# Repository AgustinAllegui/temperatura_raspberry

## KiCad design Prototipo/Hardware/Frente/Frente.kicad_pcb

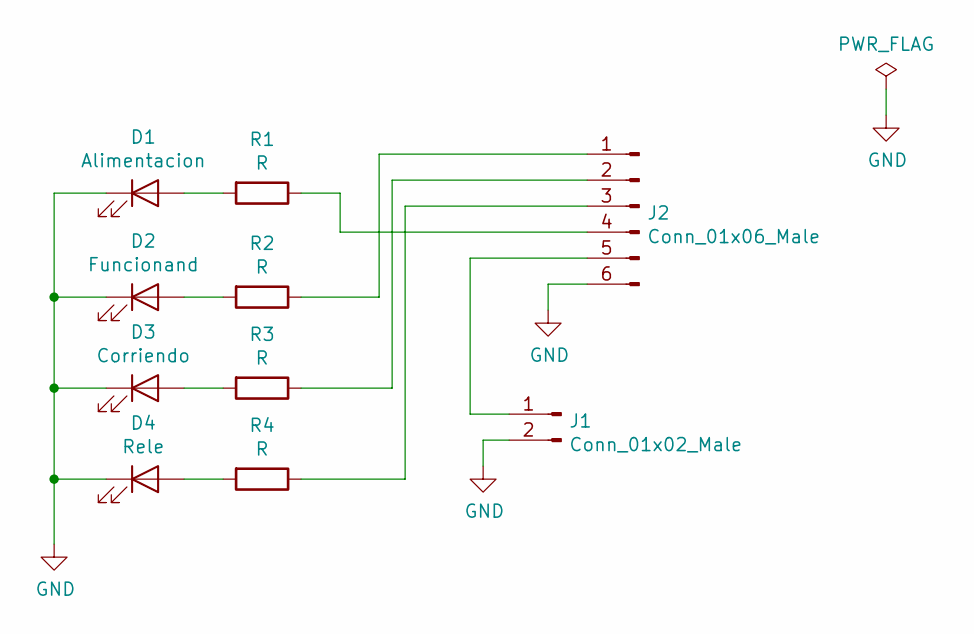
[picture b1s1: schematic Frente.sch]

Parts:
D1: Alimentacion; LED_D5.0mm
D2: Funcionand; LED_D5.0mm
D3: Corriendo; LED_D5.0mm
D4: Rele; LED_D5.0mm
J1: Conn_01x02_Male; PinHeader_1x02_P2.54mm_Horizontal
J2: Conn_01x06_Male; PinHeader_1x06_P2.54mm_Horizontal
R1, R2, R3, R4: R; R_Axial_DIN0207_L6.3mm_D2.5mm_P7.62mm_Horizontal

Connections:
GND: D1.1 (K), D2.1 (K), D3.1 (K), D4.1 (K), J1.2, J2.6
unnamed: D1.2 (A), R1.2
unnamed: D2.2 (A), R2.2
unnamed: D3.2 (A), R3.2
unnamed: D4.2 (A), R4.2
unnamed: J1.1, J2.5
unnamed: J2.1, R2.1
unnamed: J2.2, R3.1
unnamed: J2.3, R4.1
unnamed: J2.4, R1.1

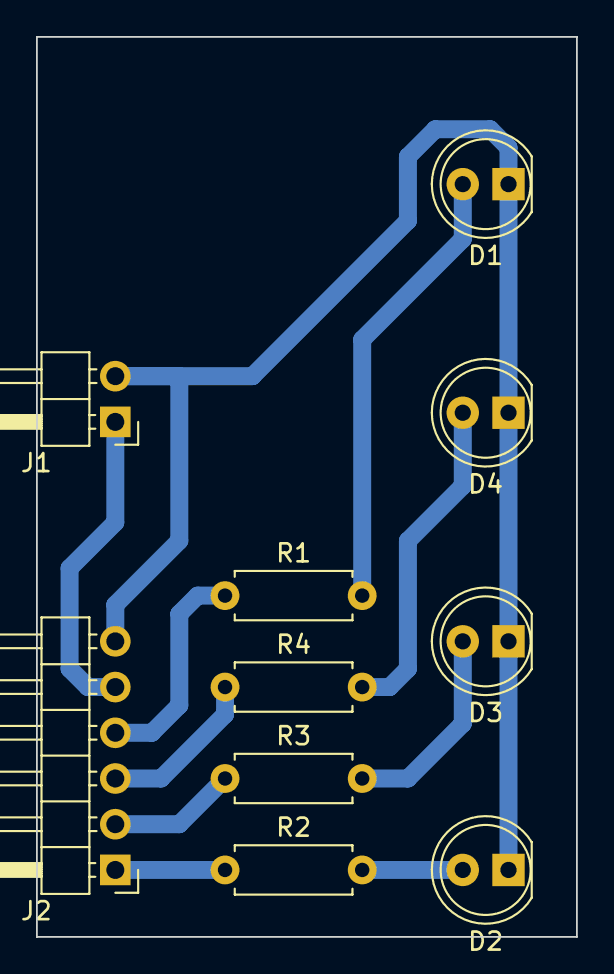
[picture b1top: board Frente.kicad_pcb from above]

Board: 2 copper layers, 30.0 x 50.0 mm, 10 parts (0 on the bottom side), 10 nets.

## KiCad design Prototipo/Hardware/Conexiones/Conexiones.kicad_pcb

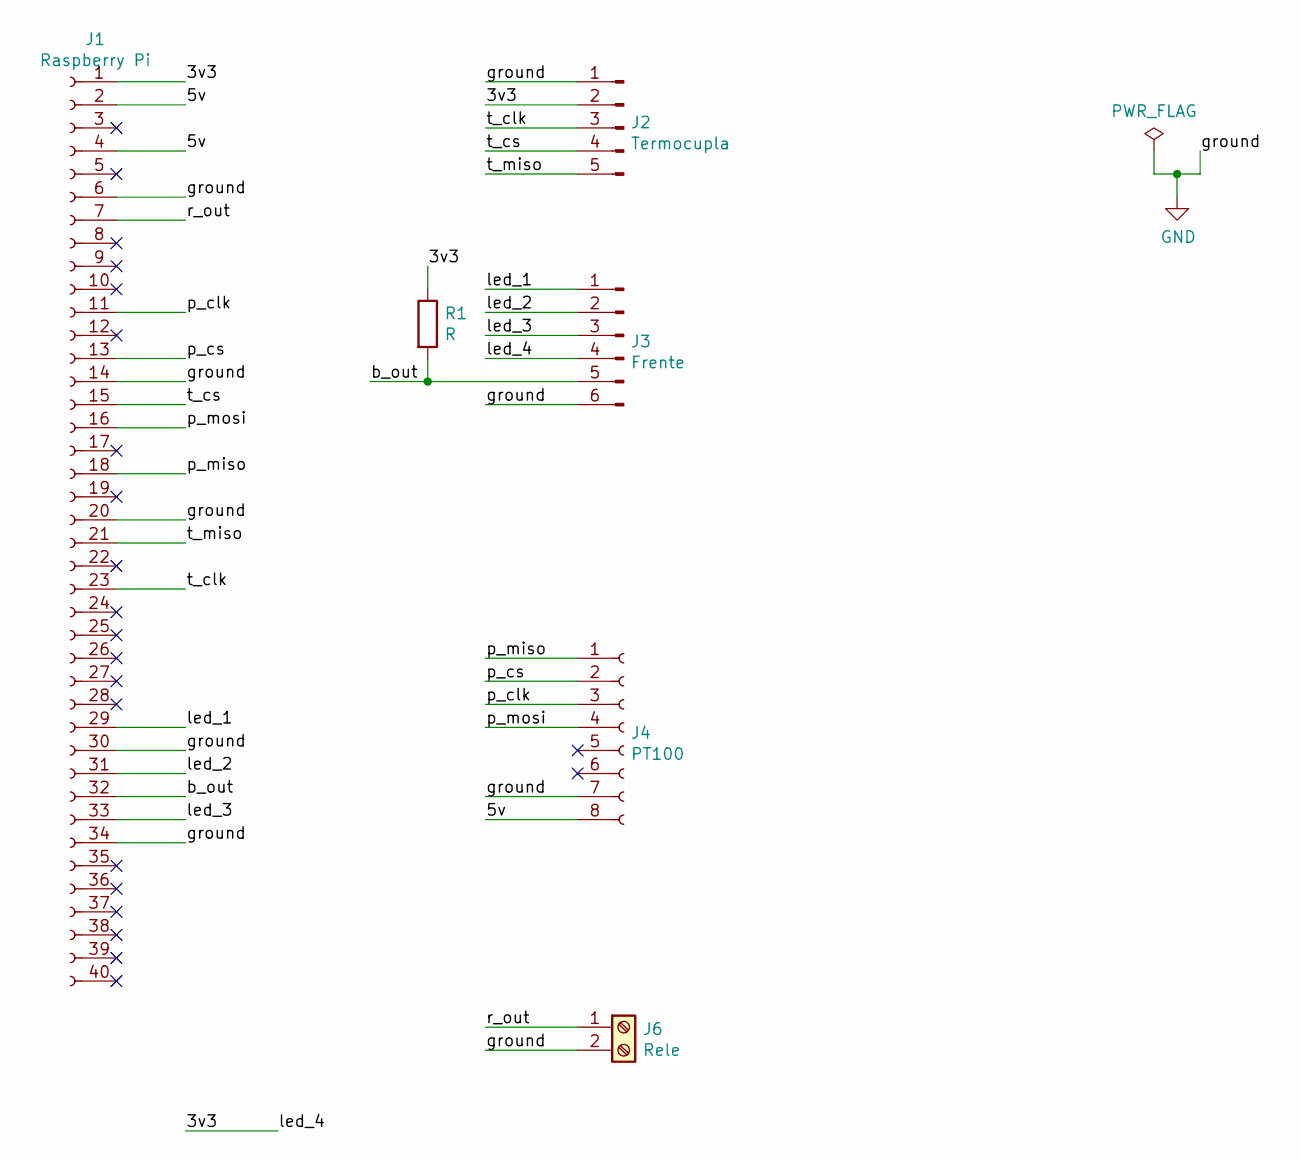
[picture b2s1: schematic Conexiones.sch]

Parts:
J1: Raspberry Pi; PinSocket_2x20_P2.54mm_Vertical
J2: Termocupla; Molex_KK-254_AE-6410-05A_1x05_P2.54mm_Vertical
J3: Frente; Molex_KK-254_AE-6410-06A_1x06_P2.54mm_Vertical
J4: PT100; PinSocket_1x08_P2.54mm_Vertical
J6: Rele; TerminalBlock_bornier-2_P5.08mm
R1: R; R_Axial_DIN0207_L6.3mm_D2.5mm_P10.16mm_Horizontal

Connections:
/3v3: J1.1, J2.2, J3.4, R1.1
/5v: J1.2, J1.4, J4.8
/b_out: J1.32, J3.5, R1.2
/led_1: J1.29, J3.1
/led_2: J1.31, J3.2
/led_3: J1.33, J3.3
/p_clk: J1.11, J4.3
/p_cs: J1.13, J4.2
/p_miso: J1.18, J4.1
/p_mosi: J1.16, J4.4
/r_out: J1.7, J6.1
/t_clk: J1.23, J2.3
/t_cs: J1.15, J2.4
/t_miso: J1.21, J2.5
GND: J1.6, J1.14, J1.20, J1.30, J1.34, J2.1, J3.6, J4.7, J6.2

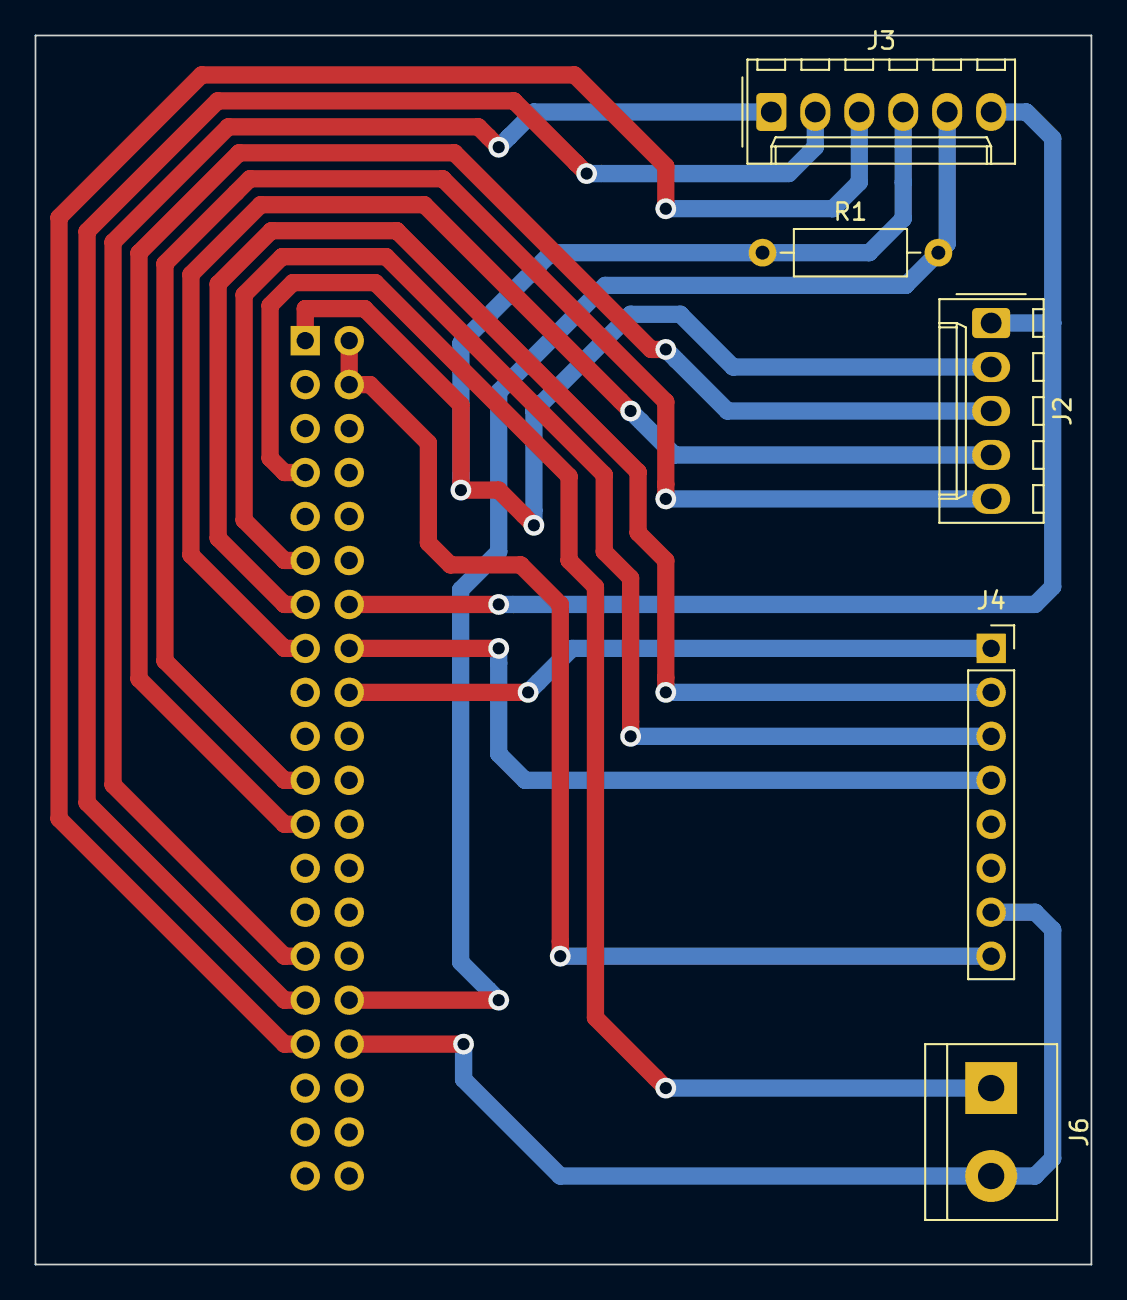
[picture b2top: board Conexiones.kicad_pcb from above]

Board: 2 copper layers, 61.0 x 71.0 mm, 6 parts (1 on the bottom side), 15 nets.

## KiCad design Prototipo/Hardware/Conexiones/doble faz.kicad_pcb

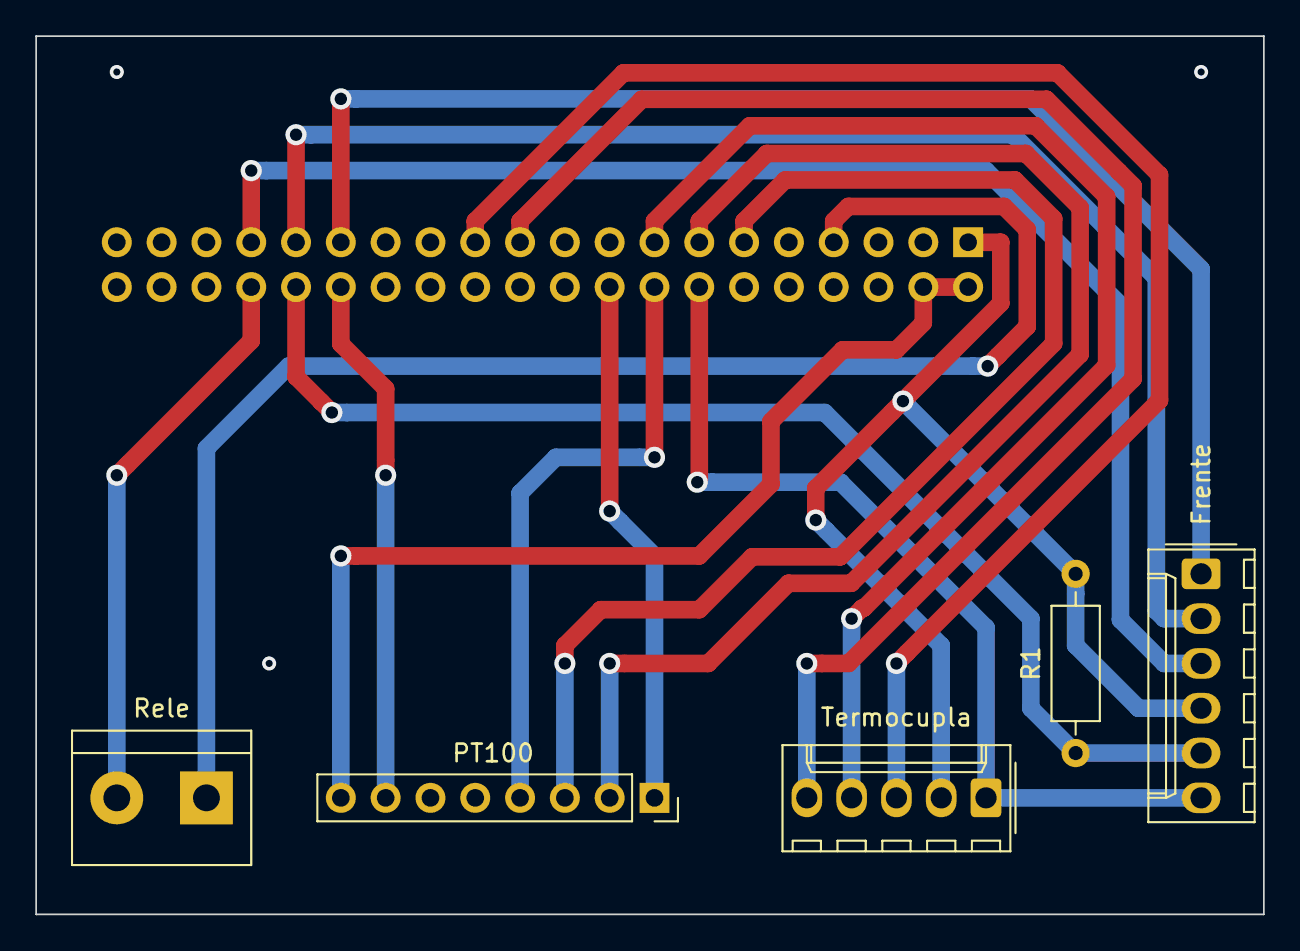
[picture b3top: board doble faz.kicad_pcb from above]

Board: 2 copper layers, 69.6 x 49.8 mm, 6 parts (1 on the bottom side), 15 nets.

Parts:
Frente: Frente; Molex_KK-254_AE-6410-06A_1x06_P2.54mm_Vertical
J1: Raspberry Pi; PinSocket_2x20_P2.54mm_Vertical
PT100: PT100; PinSocket_1x08_P2.54mm_Vertical
R1: R; R_Axial_DIN0207_L6.3mm_D2.5mm_P10.16mm_Horizontal
Rele: Rele; TerminalBlock_bornier-2_P5.08mm
Termocupla: Termocupla; Molex_KK-254_AE-6410-05A_1x05_P2.54mm_Vertical

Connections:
/3v3: Frente.4, J1.1, R1.1, Termocupla.2
/5v: J1.2, J1.4, PT100.8
/b_out: Frente.5, J1.32, R1.2
/led_1: Frente.1, J1.29
/led_2: Frente.2, J1.31
/led_3: Frente.3, J1.33
/p_clk: J1.11, PT100.3
/p_cs: J1.13, PT100.2
/p_miso: J1.18, PT100.1
/p_mosi: J1.16, PT100.4
/r_out: J1.7, Rele.1
/t_clk: J1.23, Termocupla.3
/t_cs: J1.15, Termocupla.4
/t_miso: J1.21, Termocupla.5
GND: Frente.6, J1.6, J1.14, J1.20, J1.30, J1.34, PT100.7, Rele.2, Termocupla.1

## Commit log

2019-10-09 primer commit
2019-10-09 Falta: - Sensores - Rele - Graficos - Log
    verificado:
    - referencia (valores, simple y compleja)
    - controlador PID
    - temporizacion de muestreo
    - limite de tiempo
    - resumen
2019-10-10 añadida herramienta para testear SPI (solo interfaz)
2019-10-10 spi_tester funcionando en PC
2019-10-11 herramienta para testear SPI funcionando 100%
2019-10-11 agregada la seccion documentos con algunos documentos utiles
2019-10-11 planteado el procedimiento para probar la PT100
2019-10-13 listo el protocolo para evaluar testear la lectura de PT100
2019-10-13 correcciones en herramientas
2019-10-13 modificacion en spi_tester para usar el cs con pin GPIO
2019-10-18 agregado sketch de arduino para probar SPI (todavia no implementado)
2019-10-18 spi_tester de arduino listo para probar
2019-10-19 funciones de arduino_spi_tester arregladas. todavia no funciona
2019-10-20 agregado loopback test que funciona
2019-10-20 nada
2019-10-20 añadida carpeta con librerias
2019-10-22 avance en la generacion del grafico
2019-10-22 agregado generacion de vectores en referencia
2019-10-24 grafico de supervision funcionando
2019-10-24 el grafico dibuja la referencia inicial
2019-10-24 agregado mensaje de debugueo de error
2019-10-25 implementada la entrada de la termocupla
2019-10-26 lectura con termocupla funcionando
2019-10-26 excluido el directorio de compilacion del prototipo
2019-10-26 PT100 listo para probar
2019-10-27 PT100 funcionando
2019-10-27 mejorada la seleccion del dispositivo solo cambiando CURRENT_DEVICE
2019-10-29 implementado el logger excepto el exportar a .mat
2019-10-29 graficos funcionando
2019-10-30 funcionando 100% el guardado de archivos incluyendo el *.mat
2019-10-31 cambios menores
2019-10-31 agregado limite de saturacion en la salida
2019-11-01 salida rele lista para probar
2019-11-02 archivo pid interno corregido
2019-11-02 listo para probar en una planta real
2019-11-04 bugFix: no aplicaba el tiempo correcto del actuador
2019-11-04 bugFix: la medicion de la PT100 se congaba
2019-11-05 gitignore modificado
2019-11-06 añadido archivo de configuracion ini con limites de seguridad para sensores
2019-11-11 agregada placa de conexiones
2019-11-12 añadido PCB del frente de la caja
2019-11-13 añadido manejo de los LEDs de la tapa
2019-11-13 agregados controladores para probar
2019-11-13 agregada lista con distribucion de pines
2019-11-14 designado el pin para la parada de emergencia
2019-11-18 agregada etiqueta para Leds
2019-11-18 etiqueta creada en CorelDraw
2019-11-19 agregadas todas las etiquetas
2019-11-20 cambio de los mensajes de error
2019-11-20 agregado numero de version al iniciar
2019-11-28 Implementado boton parada emergencia
    Se implementaron las funciones correspondientes al boton parada
    de emergencia presente en el frente del gabinete.
2019-11-28 Cambio numero de version a 1.0.1
2019-11-28 cambio en el mensaje de error
2019-11-28 cambiados mensajes de sensores en pantalla
2019-11-28 cambio version a 1.0.2
2019-11-28 Inicio con ventana maximizada
2019-12-02 quitado grafico de PH en resultados iniciales
2019-12-02 quitado checkbox para habilitar sensor de PH
2019-12-02 cambio numero de version a 1.0.3
2019-12-02 cambiado limite de seguridad de PT100 a 300
2019-12-02 agregado el limite de seguridad al resumen
2020-02-09 inicio de diseño placa conexiones doble faz
2020-02-14 placa doble faz lista
2020-02-24 Correccion de rutas de archivo
    Las rutas se cambiaron para que la carpeta del proyecto se encuentre en ~/.
2020-02-24 Agregado acceso directo
2020-03-03 placa de frente reducida a 5x2.5cm
2020-03-07 corregidas etiquetas de caja
2020-03-07 corregidas etiquetas
2020-03-17 Arreglados archivos de ejemplos
    - Se quitaron los controladores con PH.
    - Se dejaron solo los archivos explicados en el manual.
2020-03-20 Agregados prototipos de funciones personalizadas a la interfaz
2020-03-21 BugFix: Guardado de archivos
    - Al guardarse los archivos csv no escribia las comas.
    - Ahora, al seleccionar un filtro de archivos, lo guarda con la extension
    correspondiente
2020-03-21 minor fix
2020-03-21 minor fixes
2020-03-21 Aumentada fuente de botones de supervision
2020-09-06 Agregada constante C a algoritmo PID
